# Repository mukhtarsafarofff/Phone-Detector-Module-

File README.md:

(ENG) Mobile phone Detector is a device that can identify the existence of any active mobile phone in the vicinity and provides an indicator of the active cell phone in the vicinity.This Mobile Detector Circuit will identify incoming / outgoing calls, tweets, video communication and any SMS or GPRS use within a 1 meter radius. It can identify the mobile phone RF transmission and triggers Buzzer to produce beep sound, even though the phone is stayed in Silent mode and this alert system continues to beep until RF signals are present.In this project i use CA3130 Op-AMP IC in single supply voltage mode , so pin8 is connected to +12V and pin4 is grounded  by me , to hold it in  0V potential.

(DEU) Der Mobiltelefondetektor ist ein Gerät, das die Existenz eines aktiven Mobiltelefons in der Nähe erkennen kann und einen Indikator für das aktive Mobiltelefon in der Nähe liefert. Dieser mobile Detektorschaltkreis erkennt eingehende/ausgehende Anrufe, Tweets, Videokommunikation und alle SMS oder GPRS-Nutzung im Umkreis von 1 Meter. Es kann die HF-Übertragung des Mobiltelefons identifizieren und löst einen Buzzer aus, der einen Piepton erzeugt, auch wenn das Telefon im Lautlos-Modus bleibt und dieses Warnsystem weiterhin piept, bis HF-Signale vorhanden sind. In diesem Projekt verwende ich den CA3130 Op-AMP-IC einzeln Versorgungsspannungsmodus, also ist Pin8 mit +12V verbunden und Pin4 ist von mir geerdet, um es auf 0V-Potenzial zu halten.

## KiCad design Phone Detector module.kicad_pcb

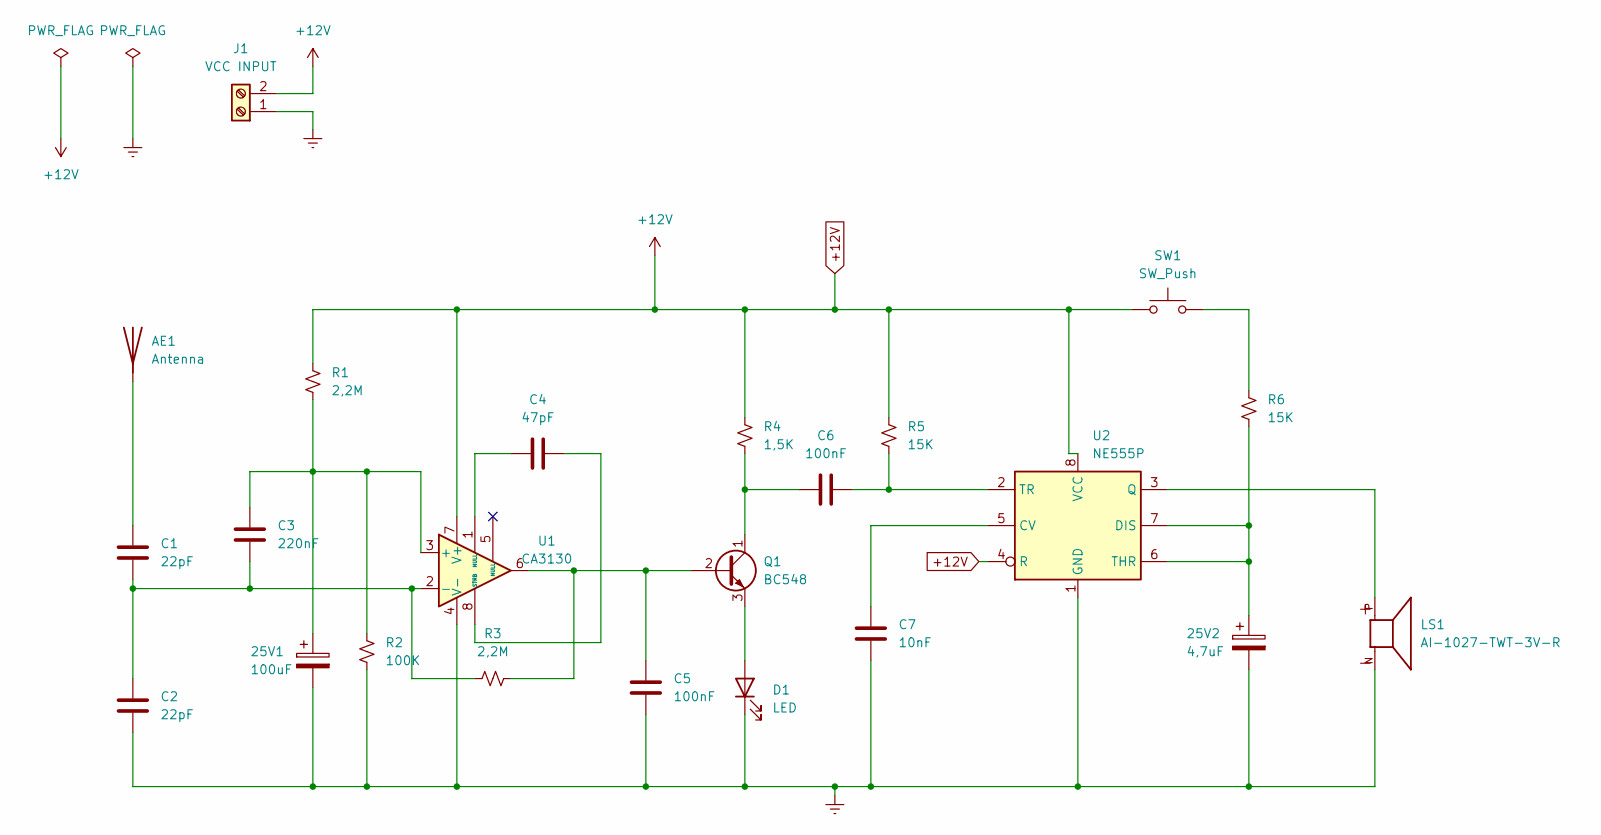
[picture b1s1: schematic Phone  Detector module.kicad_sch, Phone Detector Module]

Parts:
25V1: 100uF; CP_Radial_D13.0mm_P7.50mm
25V2: 4,7uF; CP_Radial_D13.0mm_P7.50mm
AE1: Antenna; TerminalBlock_MetzConnect_360271_1x01_Horizontal_ScrewM3.0_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
C1, C2: 22pF; C_Disc_D7.5mm_W5.0mm_P7.50mm
C3: 220nF; C_Disc_D7.5mm_W5.0mm_P7.50mm
C4: 47pF; C_Disc_D7.5mm_W5.0mm_P7.50mm
C5, C6: 100nF; C_Disc_D7.5mm_W5.0mm_P7.50mm
C7: 10nF; C_Disc_D7.5mm_W5.0mm_P7.50mm
D1: LED; LED_D5.0mm
J1: VCC INPUT; TerminalBlock_bornier-2_P5.08mm
LS1: AI-1027-TWT-3V-R; XDCR_AI-1027-TWT-3V-R; PARTREV F
Q1: BC548; TO-92_Inline
R1, R3: 2,2M; R_Axial_DIN0309_L9.0mm_D3.2mm_P15.24mm_Horizontal
R2: 100K; R_Axial_DIN0309_L9.0mm_D3.2mm_P15.24mm_Horizontal
R4: 1,5K; R_Axial_DIN0309_L9.0mm_D3.2mm_P15.24mm_Horizontal
R5, R6: 15K; R_Axial_DIN0309_L9.0mm_D3.2mm_P15.24mm_Horizontal
SW1: SW_Push; SW_MEC_5GTH9
U1: CA3130; DIP-8_W7.62mm
U2: NE555P; DIP-8_W7.62mm

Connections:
+12V: J1.2, R1.1, R4.1, R5.1, SW1.1, U1.7 (V+), U2.4 (R), U2.8 (VCC)
Earth: 25V1.2, 25V2.2, C2.2, C5.1, C7.2, D1.1 (K), J1.1, LS1.N, R2.2, U1.4 (V-), U2.1 (GND)
unnamed: AE1.1 (A), C1.1
unnamed: C4.1, U1.1 (NULL)
unnamed: D1.2 (A), Q1.3 (E)
unnamed: C5.2, Q1.2 (B), R3.2, U1.6
unnamed: C6.2, Q1.1 (C), R4.2
unnamed: R6.1, SW1.2
unnamed: 25V1.1, C3.2, R1.2, R2.1, U1.3 (+)
unnamed: C1.2, C2.1, C3.1, R3.1, U1.2 (-)
unnamed: C4.2, U1.8 (STRB)
unnamed: C7.1, U2.5 (CV)
unnamed: 25V2.1, R6.2, U2.6 (THR), U2.7 (DIS)
unnamed: LS1.P, U2.3 (Q)
unnamed: C6.1, R5.2, U2.2 (TR)

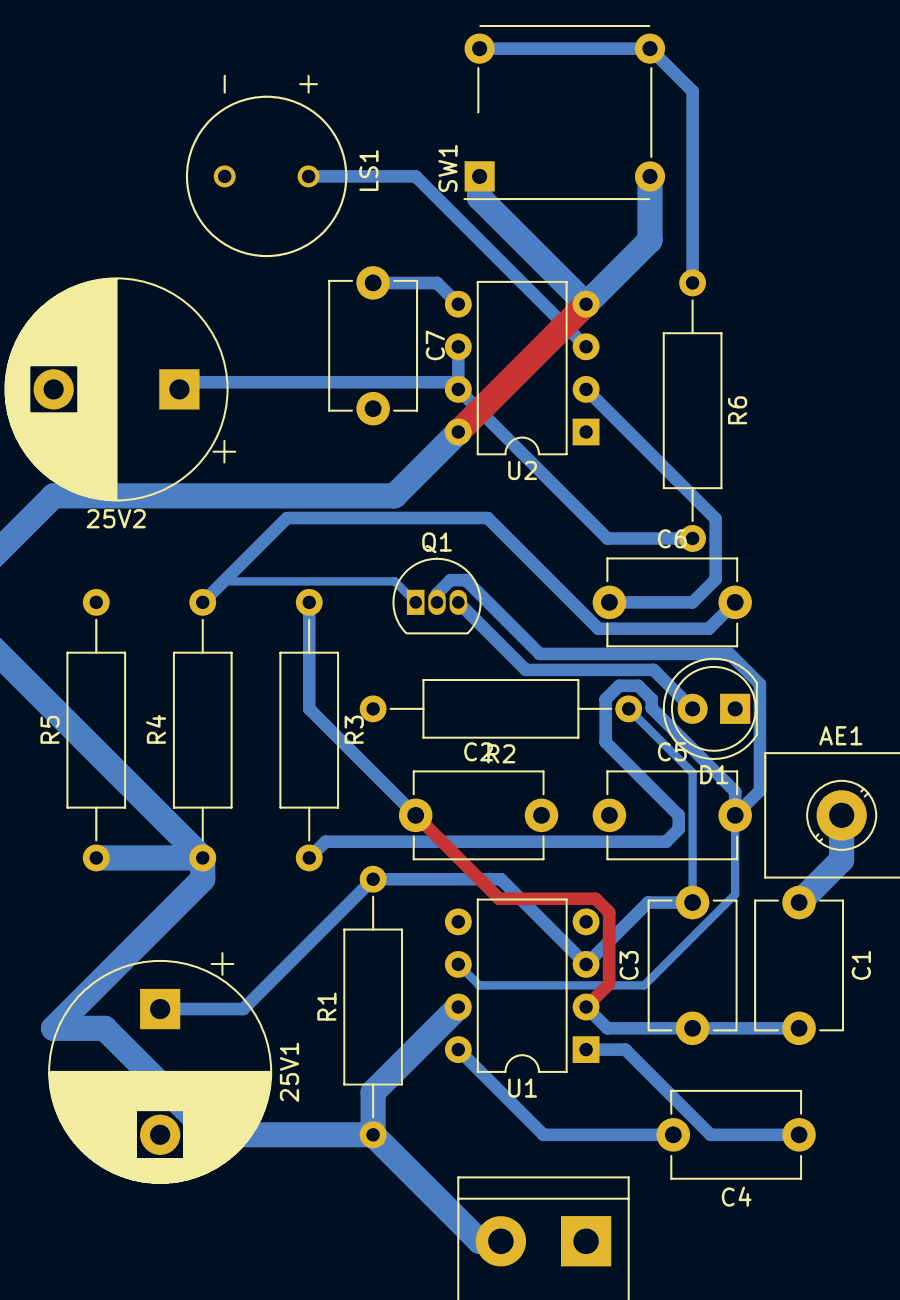
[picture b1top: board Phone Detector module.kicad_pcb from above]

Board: 2 copper layers, 23 parts (0 on the bottom side), 15 nets.

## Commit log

2024-03-28 Phone Detector Module is accomplished
